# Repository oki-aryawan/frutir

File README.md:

##  IoT Fruit Sorting System (Cherry Tomato) with TCS3200 and ESP32

## Hardware
- ESP32
- TCS3200
- Servo SG90
- LCD 16x2 I2C
- Motor DC (2)

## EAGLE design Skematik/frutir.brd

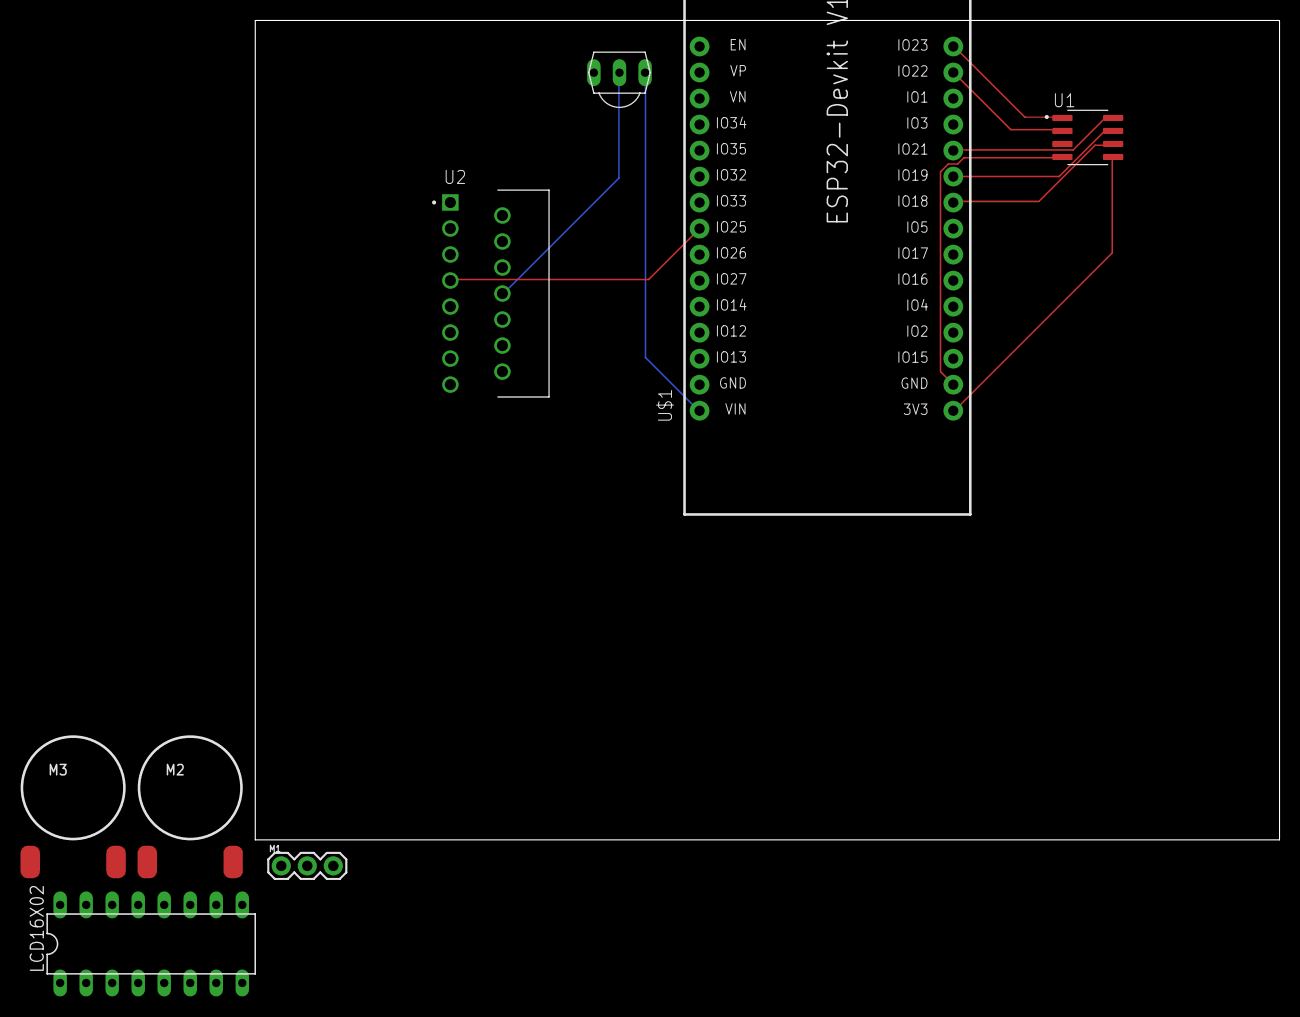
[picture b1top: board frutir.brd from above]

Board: 2 copper layers, 100.0 x 80.0 mm, 8 parts (0 on the bottom side), 18 nets.

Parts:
LCD16X02: PCF8574AP; DIL16
M1: SERVO; 1X03
M2, M3: MOTORSHORT; VIBE-MOTOR-10MM-SMD
U1: TCS3200; SOIC127P600X175-8N
U2: L298N; TO127P2020X500X2100-15
U$1: ESP32DEVKITV1; ESP32-DEVKITV1
U$2: TSOP1830; TSOP18XX

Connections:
unnamed: U1.1, U$1.15
unnamed: U1.2, U$1.7
unnamed: U1.7, U$1.10
unnamed: U1.8, U$1.8
unnamed: U1.6, U$1.6
unnamed: U1.5, U$1.1
unnamed: U1.4, U$1.2
unnamed: LCD16X02.8, M1.3, U2.8, U$1.28, U$2.GND
unnamed: LCD16X02.16, M1.2, U$1.30, U$2.VCC
unnamed: U$1.28, U$2.OUT
unnamed: U2.6, U$1.24
unnamed: U2.5, U$1.24
unnamed: U2.7, U$1.23
unnamed: M2.+, M3.+, U2.2
unnamed: M2.-, M3.-, U2.3
unnamed: M1.1, U$1.20
unnamed: LCD16X02.15, U$1.11
unnamed: LCD16X02.14, U$1.14

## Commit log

2023-06-13 astungkara
2023-06-15 final
2024-06-29 docs

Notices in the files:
parts and their libraries:
SparkFun-Electromechanical: Licensing: Creative Commons ShareAlike 4.0 International - https://creativecommons.org/licenses/by-sa/4.0
